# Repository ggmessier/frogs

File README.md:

# Fun Frog Project Repository
This repository is for Geoff's various fun projects described in a bit more detail [here](https://lib.engineer/pages/diversions).  Much of my projects are frog themed due to a long time love of [Kermit](https://en.wikipedia.org/wiki/Kermit_the_Frog) and their [role in our ecosystems](https://www.naturewatch.ca/wp-content/biguploads/senior_guide_712.pdf).

## Structure
- `src`: Software source code.
- `boards`: Printed circuit board CAD files.
- `mech`: 3D printer mechanical CAD files.

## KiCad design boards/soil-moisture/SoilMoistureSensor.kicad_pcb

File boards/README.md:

# frogs - boards
All active boards are designed using [KiCad](https://www.kicad.org/). `eagle` contains some legacy boards designed using Eagle.  My custom symbol library is located in `lib` and custom footprint library is in `lib/lib.pretty`.  On a new KiCad install, these custom libraries are added under the Preferences library but the symbol libraries must be added in the schematic editor and the footprint libraries added in the PCB editor.

## Directories

- `dAuratus`: AVR128DB28 MCU board.
- `ils-avr`: AVR128DB28 DIP board used for ENCM 369.
- `soil-moisture`: A capacitive soil moisture sensor.
- `tile`: Files used to tile multiple PCBs for fabrication.

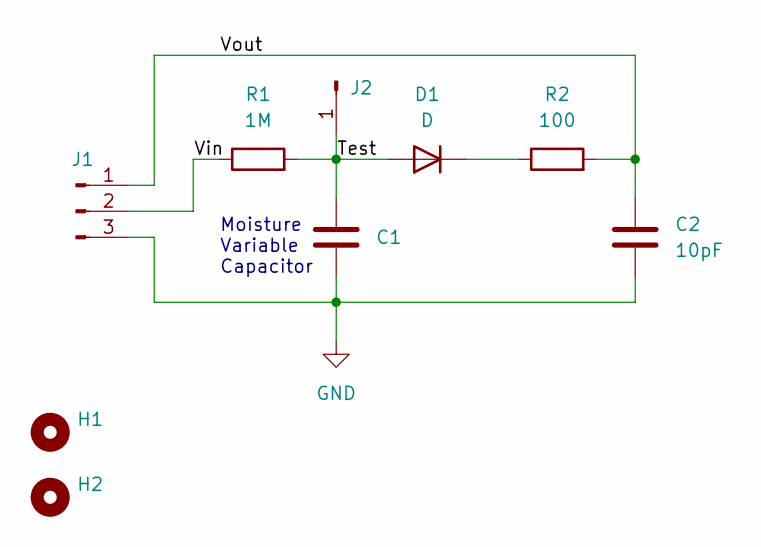
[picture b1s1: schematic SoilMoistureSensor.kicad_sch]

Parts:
C1: C; Moisture_Capacitor
C2: 10pF; C_Disc_D4.3mm_W1.9mm_P5.00mm
D1: D; D_A-405_P7.62mm_Horizontal
H1, H2: MountingHole; MountingHole_2.2mm_M2
J1: Conn_01x03_Male; PinHeader_1x03_P2.54mm_Vertical
J2: Conn_01x01_Male; PinHeader_1x01_P2.54mm_Vertical
R1: 1M; R_Axial_DIN0207_L6.3mm_D2.5mm_P2.54mm_Vertical
R2: 100; R_Axial_DIN0207_L6.3mm_D2.5mm_P2.54mm_Vertical

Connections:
/Test: C1.1, D1.2 (A), J2.1, R1.2
/Vin: J1.2, R1.1
/Vout: C2.1, J1.1, R2.2
GND: C1.2, C2.2, J1.3
unnamed: D1.1 (K), R2.1

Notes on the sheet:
Moisture Variable Capacitor

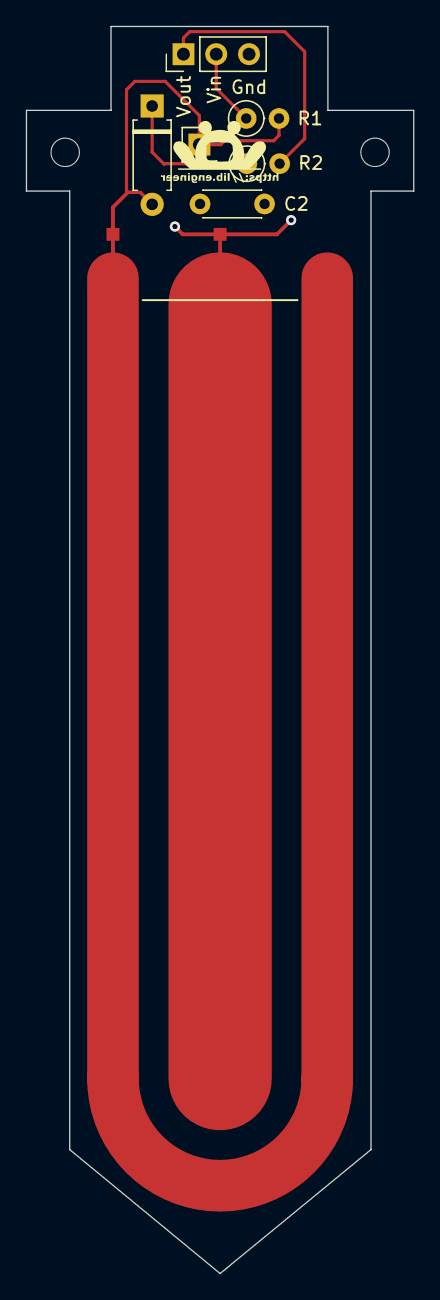
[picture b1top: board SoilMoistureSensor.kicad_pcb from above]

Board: 2 copper layers, 30.0 x 96.6 mm, 9 parts (0 on the bottom side), 5 nets.

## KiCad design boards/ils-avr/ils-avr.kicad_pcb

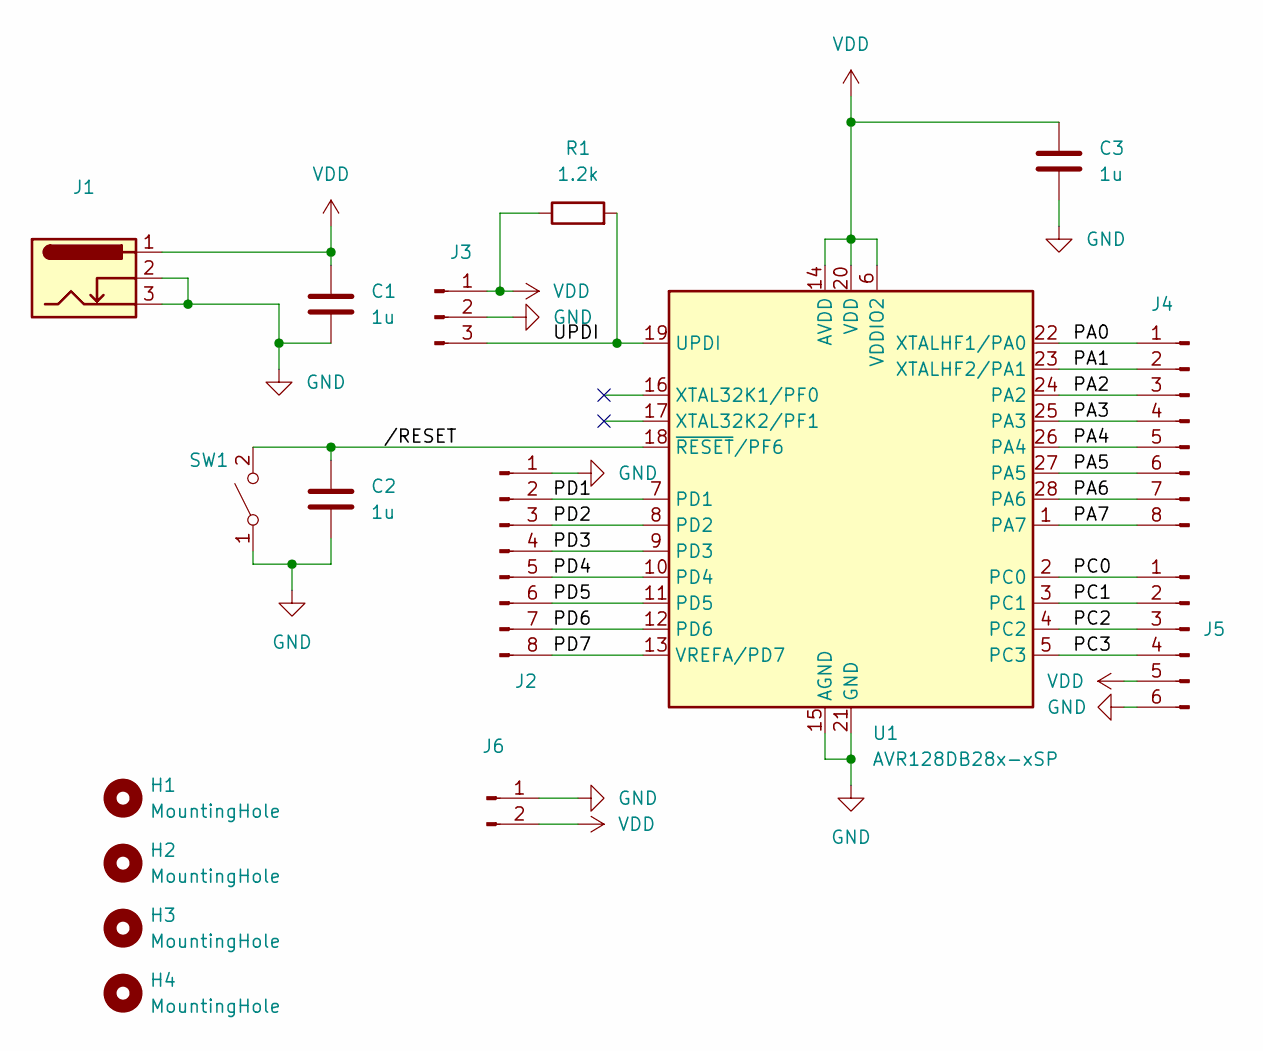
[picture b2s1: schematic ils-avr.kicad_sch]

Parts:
C1, C2, C3: 1u; C_Disc_D7.5mm_W2.5mm_P5.00mm
H1, H2, H3, H4: MountingHole; MountingHole_3.2mm_M3
J1: Barrel_Jack_Switch_Pin3Ring; BarrelJack_Kycon_KLDX-0202-xC_Horizontal
J2, J4: Conn_01x08_Male; PinHeader_1x08_P2.54mm_Vertical
J3: Conn_01x03_Male; PinHeader_1x03_P2.54mm_Vertical
J5: Conn_01x06_Male; PinHeader_1x06_P2.54mm_Vertical
J6: Conn_01x02_Male; PinHeader_1x02_P2.54mm_Vertical
R1: 1.2k; R_Axial_DIN0309_L9.0mm_D3.2mm_P12.70mm_Horizontal
SW1: SW_SPST; SW_PUSH_6mm
U1: AVR128DB28x-xSP; DIP-28_W7.62mm

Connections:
/PA0: J4.1, U1.22 (XTALHF1/PA0)
/PA1: J4.2, U1.23 (XTALHF2/PA1)
/PA2: J4.3, U1.24 (PA2)
/PA3: J4.4, U1.25 (PA3)
/PA4: J4.5, U1.26 (PA4)
/PA5: J4.6, U1.27 (PA5)
/PA6: J4.7, U1.28 (PA6)
/PA7: J4.8, U1.1 (PA7)
/PC0: J5.1, U1.2 (PC0)
/PC1: J5.2, U1.3 (PC1)
/PC2: J5.3, U1.4 (PC2)
/PC3: J5.4, U1.5 (PC3)
/PD1: J2.2, U1.7 (PD1)
/PD2: J2.3, U1.8 (PD2)
/PD3: J2.4, U1.9 (PD3)
/PD4: J2.5, U1.10 (PD4)
/PD5: J2.6, U1.11 (PD5)
/PD6: J2.7, U1.12 (PD6)
/PD7: J2.8, U1.13 (VREFA/PD7)
/UPDI: J3.3, R1.2, U1.19 (UPDI)
//RESET: C2.1, SW1.2 (B), U1.18 (~RESET/PF6)
GND: C1.2, C2.2, C3.2, J1.2, J1.3, J2.1, J3.2, J5.6, J6.1, SW1.1 (A), U1.15 (AGND), U1.21 (GND)
VDD: C1.1, C3.1, J1.1, J3.1, J5.5, J6.2, R1.1, U1.6 (VDDIO2), U1.14 (AVDD), U1.20 (VDD)

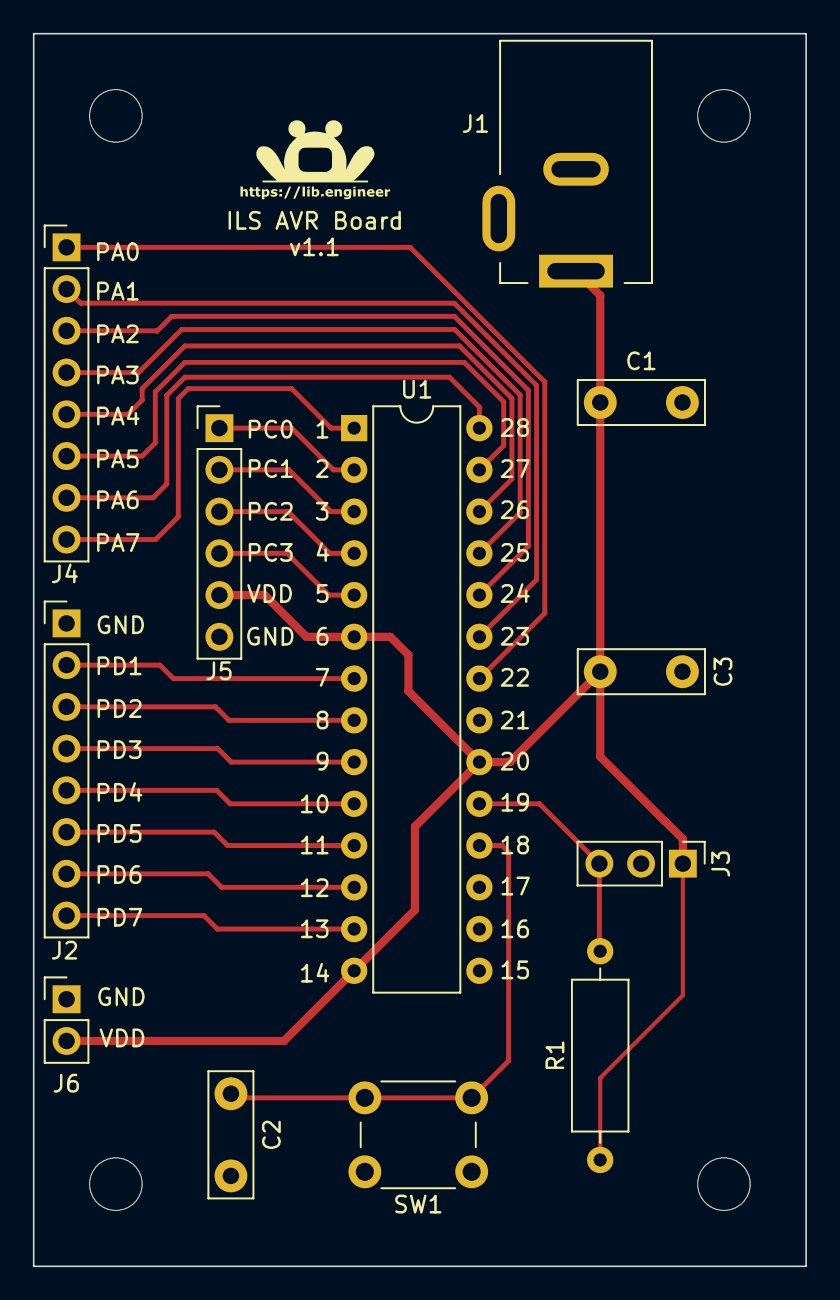
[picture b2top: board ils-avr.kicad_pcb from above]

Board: 2 copper layers, 47.0 x 75.0 mm, 16 parts (0 on the bottom side), 23 nets.

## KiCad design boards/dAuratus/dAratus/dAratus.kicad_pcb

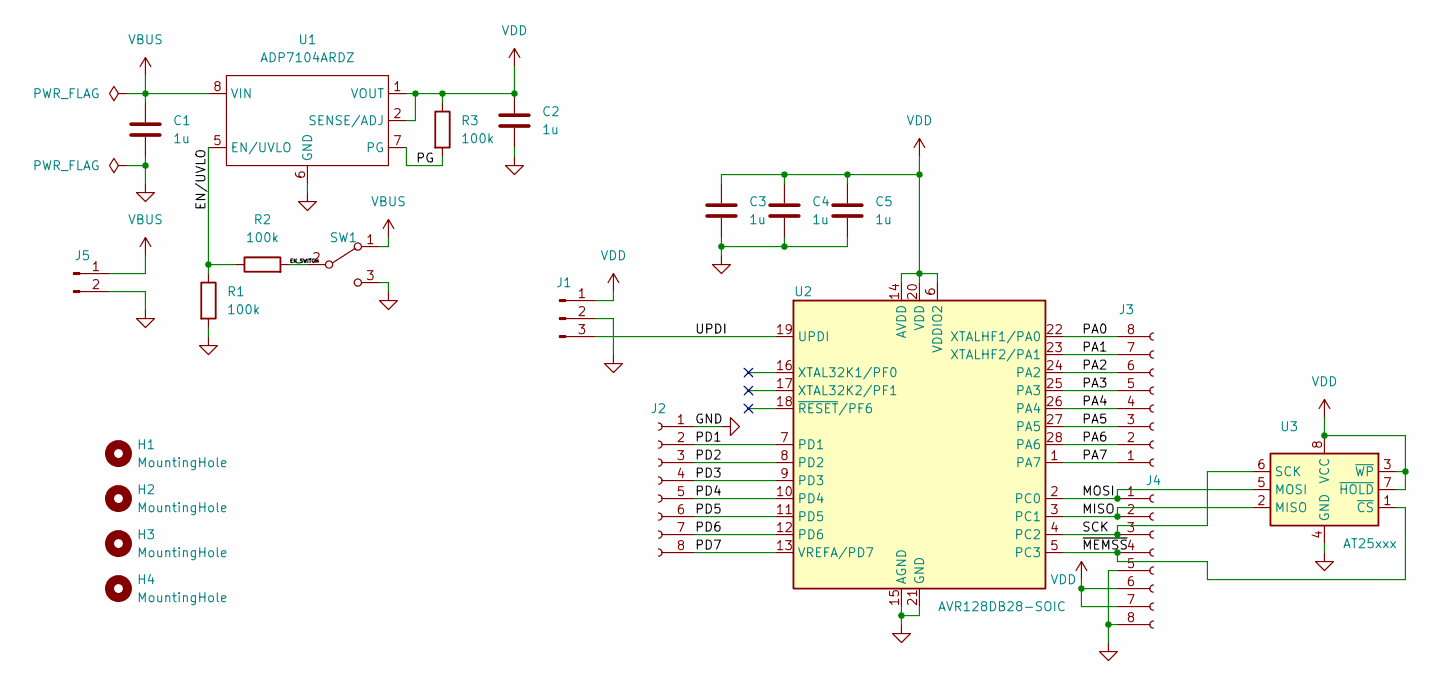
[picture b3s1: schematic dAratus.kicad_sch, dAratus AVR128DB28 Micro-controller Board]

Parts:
C1, C2, C3, C4, C5: 1u; C_0805_2012Metric
H1, H2, H3, H4: MountingHole; MountingHole_3.2mm_M3
J1: Conn_01x03_Male; PinHeader_1x03_P2.54mm_Vertical
J2, J3, J4: Conn_01x08_Female; PinHeader_1x08_P2.54mm_Vertical
J5: Conn_01x02_Male; PinHeader_1x02_P2.54mm_Vertical
R1, R2, R3: 100k; R_0805_2012Metric
SW1: SW_SPDT; EAO_SPDT_90_10290
U1: ADP7104ARDZ
U2: AVR128DB28-SOIC; SOIC-28W_7.5x17.9mm_P1.27mm
U3: AT25xxx; SOIC-8_3.9x4.9mm_P1.27mm

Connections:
/EN_SWITCH: R2.2, SW1.2 (B)
/EN/UVLO: R1.1, R2.1, U1.5 (EN/UVLO)
/MISO: J4.2, U2.3 (PC1), U3.2 (MISO)
/MOSI: J4.1, U2.2 (PC0), U3.5 (MOSI)
/PA0: J3.8, U2.22 (XTALHF1/PA0)
/PA1: J3.7, U2.23 (XTALHF2/PA1)
/PA2: J3.6, U2.24 (PA2)
/PA3: J3.5, U2.25 (PA3)
/PA4: J3.4, U2.26 (PA4)
/PA5: J3.3, U2.27 (PA5)
/PA6: J3.2, U2.28 (PA6)
/PA7: J3.1, U2.1 (PA7)
/PD1: J2.2, U2.7 (PD1)
/PD2: J2.3, U2.8 (PD2)
/PD3: J2.4, U2.9 (PD3)
/PD4: J2.5, U2.10 (PD4)
/PD5: J2.6, U2.11 (PD5)
/PD6: J2.7, U2.12 (PD6)
/PD7: J2.8, U2.13 (VREFA/PD7)
/PG: R3.2, U1.7 (PG)
/SCK: J4.3, U2.4 (PC2), U3.6 (SCK)
/UPDI: J1.3, U2.19 (UPDI)
/~MEMSS: J4.4, U2.5 (PC3), U3.1 (~CS)
GND: C1.2, C2.2, C3.2, C4.2, C5.2, J1.2, J2.1, J4.5, J4.8, J5.2, R1.2, SW1.3 (C), U1.3 (GND3), U1.6 (GND), U1.9 (EPAD), U2.15 (AGND), U2.21 (GND), U3.4 (GND)
VBUS: C1.1, J5.1, SW1.1 (A), U1.8 (VIN)
VDD: C2.1, C3.1, C4.1, C5.1, J1.1, J4.6, J4.7, R3.1, U1.1 (VOUT), U1.2 (SENSE/ADJ), U2.6 (VDDIO2), U2.14 (AVDD), U2.20 (VDD), U3.3 (~WP), U3.7 (~HOLD), U3.8 (VCC)

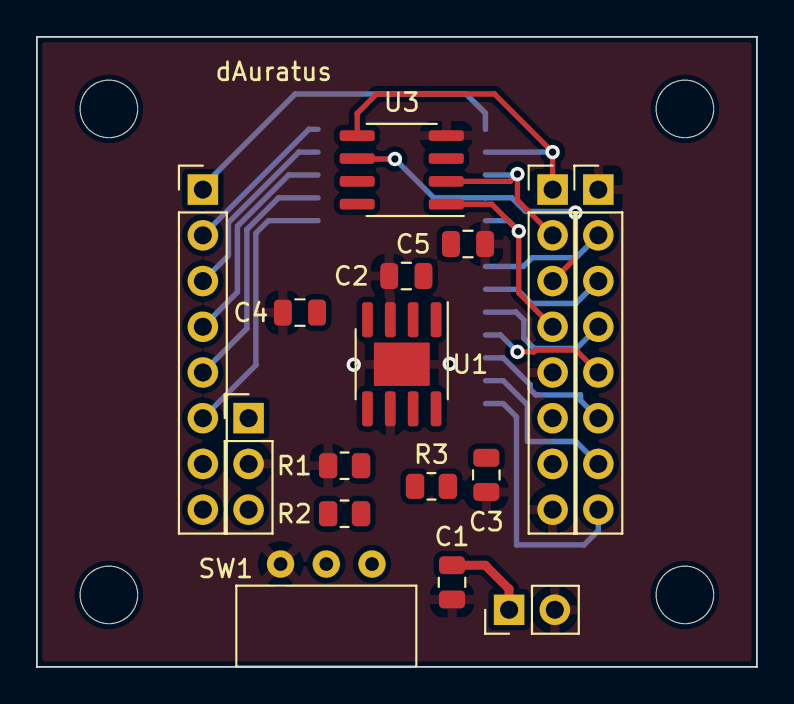
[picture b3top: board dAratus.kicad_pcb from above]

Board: 2 copper layers, 40.0 x 35.0 mm, 21 parts (1 on the bottom side), 26 nets.

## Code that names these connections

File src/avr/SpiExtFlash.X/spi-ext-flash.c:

/*
 * File:   spi-ext-flash.c
 * Author: gmessier
 *
 * Created on December 28, 2022, 1:59 PM
 */


#include <stdio.h>
#include <string.h>
#include <avr/io.h>
#include "../lib-Avr128DbX.X/lib-avr.h"


void TestSpi(){
    
//    SpiFlashWriteEnable();
    
//    USART_PRINT_STR("done!\n\r");
    
    
    SELECT_FLASH_CHIP;
    SPI_TX_BYTE(0x06);
    DESELECT_FLASH_CHIP;

    char str[30];
    sprintf(str,"\n\r0x%x\n\r",SpiFlashReadStatus(1));
    USART_PRINT_STR(str);

    sprintf(str,"0x%x\n\r",SpiFlashReadStatus(1));
    USART_PRINT_STR(str);

    sprintf(str,"0x%x\n\r",SpiFlashReadStatus(1));
    USART_PRINT_STR(str);

    DESELECT_FLASH_CHIP;
            
}


int main(void) {
    
    // Use the internal 32.768kHz oscillator.
    CCP = 0xd8;
    CLKCTRL.MCLKCTRLA = 0x01;
    while( CLKCTRL.MCLKSTATUS & 0b00000001 ){
        ;
    }
    
    // Configure PA3 as the FLASH SPI select output.
    PORTA.DIRSET = 0b00001000;   
    DESELECT_FLASH_CHIP;
    
    
    // Enable SPI, master mode, double clock mode.
    SPI0.CTRLA = 0b00110001;
    
    // Non-buffered (normal) mode,
    // disable slave select line, SPI Mode 0.
    SPI0.CTRLB = 0b01000100;
    
    // Enable normal mode interrupts.
    SPI0.INTCTRL = 0b00000001;
 


    // -- SPI Configuration --
    // SCLK: PA6
    // MISO (Master In, Slave Out): PA5
    // MOSI (Master Out, Slave In): PA4
    PORTA.DIRSET = 0b01010000;
    
    SELECT_FLASH_CHIP;
    SPI0.DATA = 0x66; 
    
    while( (SPI0.INTFLAGS & 0x80) == 0){ ; }

    DESELECT_FLASH_CHIP;

    
    // -- UART Configuration --
    // 2400 baud
    USART0.BAUD = 0x006d;
    
    // Enable Data Register Empty Interrupt Flag (DREIF).
    USART0.CTRLA = 0b00100000;
        
    // Asynchronous, 8N1 (8 data, no parity, 1 stop)
    USART0.CTRLC = 0b00000011;
    
    // Configure PA0 as an output for TxD.
    PORTA.DIRSET = 0b00000001;

    // Enable transmitter, receiver and double speed mode.
    USART0.CTRLB = 0b11000010;
        
    uint8_t uartMenuSize = 1;
    uint8_t help0[] = "Test SPI.";
    
    UartCommand uartMenu[] = {
        { 0, help0, &TestSpi }
    };
    
    while (1) {
        USART_MENU_PROMPT;
        USART_READ_MENU_COMMAND;        
    }
    
    
}

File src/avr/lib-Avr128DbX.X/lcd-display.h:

/* 
 * File:   lcd-display.h
 * Author: gmessier
 * Routines for based LCD displays.
 */

#ifndef LCD_DISPLAY_H
#define	LCD_DISPLAY_H

#include <avr/io.h>

// Control Routines for a 2 Line LCD Display (ST7066U Driver Chip)

/* Notes:
 * - Tested only for the 32.786kHz internal oscillator.  May need to add
 *   control line and/or E line delays for faster clocks.
 * - LCD tends to be put in a weird state when loading new code into the AVR.
 *   A clean screen init usually requires a reset/power cycle.
 * - Careful of having peripherals connected (ie. usb to uart) that partially
 *   power the chip and prevent a clean reset.
 */


/*
 * LCD Pin Mapping:
 *  PD7: E
 *  PD6: RW
 *  PD5: RS
 *  PA4-PA7: DB4-DB7
 */
#define LCD_PINS_PD5_TO_7_PA4_TO_7 { \
  PORTD.DIRSET = 0b11100000; \
  PORTA.DIRSET = 0b11110000; \
}

/*
 * Approximate 1 sec startup delay assuming
 * 32.768k internal oscillator and 5 instructions
 * per loop iteration.
 */
#define LCD_STARTUP_DELAY_32K_OSC { \
  for(uint16_t cc=0; cc < 6553; cc++ ) ; \
}

// Control Pin Set/Clear Routines
#define LCD_SET_E { PORTD.OUT |= 0b10000000; }
#define LCD_CLR_E { PORTD.OUT &= 0b01111111; }
#define LCD_SET_RW { PORTD.OUT |= 0b01000000; }
#define LCD_CLR_RW { PORTD.OUT &= 0b10111111; }
#define LCD_SET_RS { PORTD.OUT |= 0b00100000; }
#define LCD_CLR_RS { PORTD.OUT &= 0b11011111; }


/*
 * Block while LCD is busy.
 * 1. Set DB7 pin to input.
 * 2. Set control lines.
 * 3. Loop while busy.  DB7 read while E is high.  Need a second E cycle
 *    to clear the AC information from the input pin due to being in 4 bit mode.
 * 4. Set DB7 back to an output line.
 */
#define LCD_BLK { \
    PORTA.DIRCLR = 0b10000000; \
    LCD_CLR_RS; \
    LCD_SET_RW; \
    uint8_t rd; \
    do{ \
      LCD_SET_E; \
      rd = PORTA.IN & 0b10000000; \
      LCD_CLR_E; \
      LCD_SET_E; \
      LCD_CLR_E; \
    }while(rd); \
    PORTA.DIRSET = 0b10000000; \
}

/*
 * Write data to the LCD in 4 bit transfer mode.  Assumes control bits
 * already set to enable either a character or control command.
 */  
#define LCD_WRITE(d) { \
    LCD_SET_E; \
    PORTA.OUT &= 0x0f; \
    PORTA.OUT |= 0xf0 & (d); \
    LCD_CLR_E; \
    LCD_SET_E; \
    PORTA.OUT &= 0x0f; \
    PORTA.OUT |= 0xf0 & ( d << 4 ); \
    LCD_CLR_E; \
}

/*
 * Write control command to LCD in 4 bit transfer mode.
 */
#define LCD_CMD(d) { \
    LCD_BLK; \
    LCD_CLR_RW; \
    LCD_CLR_RS; \
    LCD_WRITE(d); \
}
/*
 * Write character to LCD in 4 bit transfer mode.
 */
#define LCD_CHAR(d) { \
    LCD_BLK; \
    LCD_CLR_RW; \
    LCD_SET_RS; \
    LCD_WRITE(d); \
}

/*
 * Initialize LCD screen.
 * 1. Set to 8 bit mode (0x30).  Do this twice in case the LCD initializes
 *    to 4 bit mode and expects two transfers.
 * 2. Set to 4 bit mode (0x20).  Single transfer since we're in 8 bit mode.
 * 3. Set to 4 bit, 2 line mode (0x28).
 * 4. Turn on display with no cursor (0x0c).
 * 5. Clear display (0x01).
 */
#define LCD_INIT_4PIN_2LINE { \
  LCD_CLR_RW; \
  LCD_CLR_RS; \
  LCD_SET_E; \
  PORTA.OUT &= 0b00001111; \
  PORTA.OUT |= 0b00110000; \
  LCD_CLR_E; \
  LCD_SET_E; \
  LCD_CLR_E; \
  LCD_SET_E; \
  PORTA.OUT &= 0b00001111; \
  PORTA.OUT |= 0b00100000; \
  LCD_CLR_E; \
  LCD_CMD(0x28); \
  LCD_CMD(0x0c); \
  LCD_CMD(0x01); \
}


/*
 * Print a string to the top line.
 */
#define LCD_PRINT_TOP(x) { \
  LCD_CMD(0x80); \
  uint8_t lcd_cc = 0; \
  while( (lcd_cc<8) && ((x)[lcd_cc]!=0) ){ \
    LCD_CHAR((x)[lcd_cc]); \
    lcd_cc++; \
  } \
  while( lcd_cc<8 ){ \
    LCD_CHAR(' '); \
    lcd_cc++; \
  } \
}

/*
 * Print a string to the bottom line.
 */
#define LCD_PRINT_BOTTOM(x) { \
  LCD_CMD(0xc0); \
  uint8_t lcd_cc = 0; \
  while( (lcd_cc<8) && ((x)[lcd_cc]!=0) ){ \
    LCD_CHAR((x)[lcd_cc]); \
    lcd_cc++; \
  } \
  while( lcd_cc<8 ){ \
    LCD_CHAR(' '); \
    lcd_cc++; \
  } \
}


#endif

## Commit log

2018-05-18 Init dir structure and Rev 1.0 of FrogBrain.
2018-05-31 Final rev 1.0 brain and initial tadpole breadboard.
2018-05-31 Fixing README tables.
2018-05-31 Error in tadpole BOM.
2018-07-27 Added rev1.1 of the frog brain.
2018-08-20 Kermit PIC protocol and small frogbrain board mods.
2019-05-06 Post ILS code modifications (needs cleaning).
2019-05-06 Added GUI directory and modified ILS player files.
2020-05-26 Gandalf sync. 3D print additions.
2020-06-22 File clean-up and GUI repository merge.
2020-06-22 Updated GUI README.
2020-08-04 BBB GPIO code, makey head and dir reorg.
2022-12-11 Re-organization (long overdue push).
2022-12-22 dAuratus board development begins. AVR code cleanup.
2022-12-28 AVR UART menu code and AVR library framework added.
2023-04-07 Version 1.0 of fan control software.
2023-07-16 Soil moisture spice simulation. Some AVR code mods.
2024-01-14 Huge update, long overdue.
2024-11-30 Long overdue update: PCB directory cleanup, ILS board modifications, misc household 3D print projects, AVR code for fan control and temperature sensing.
